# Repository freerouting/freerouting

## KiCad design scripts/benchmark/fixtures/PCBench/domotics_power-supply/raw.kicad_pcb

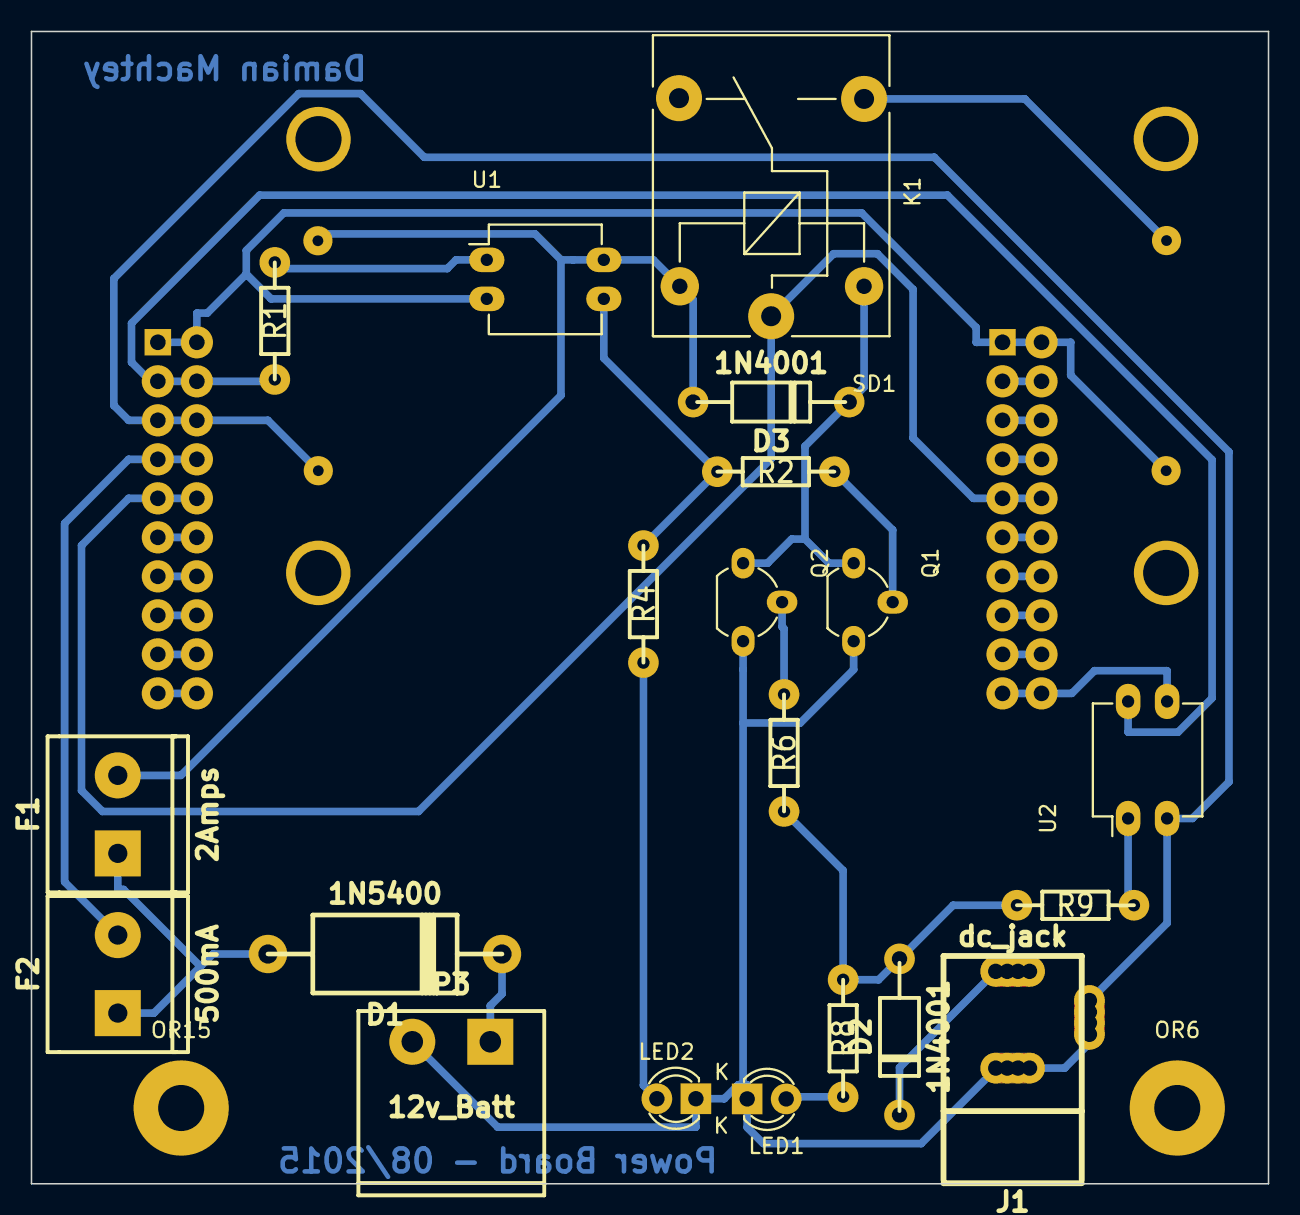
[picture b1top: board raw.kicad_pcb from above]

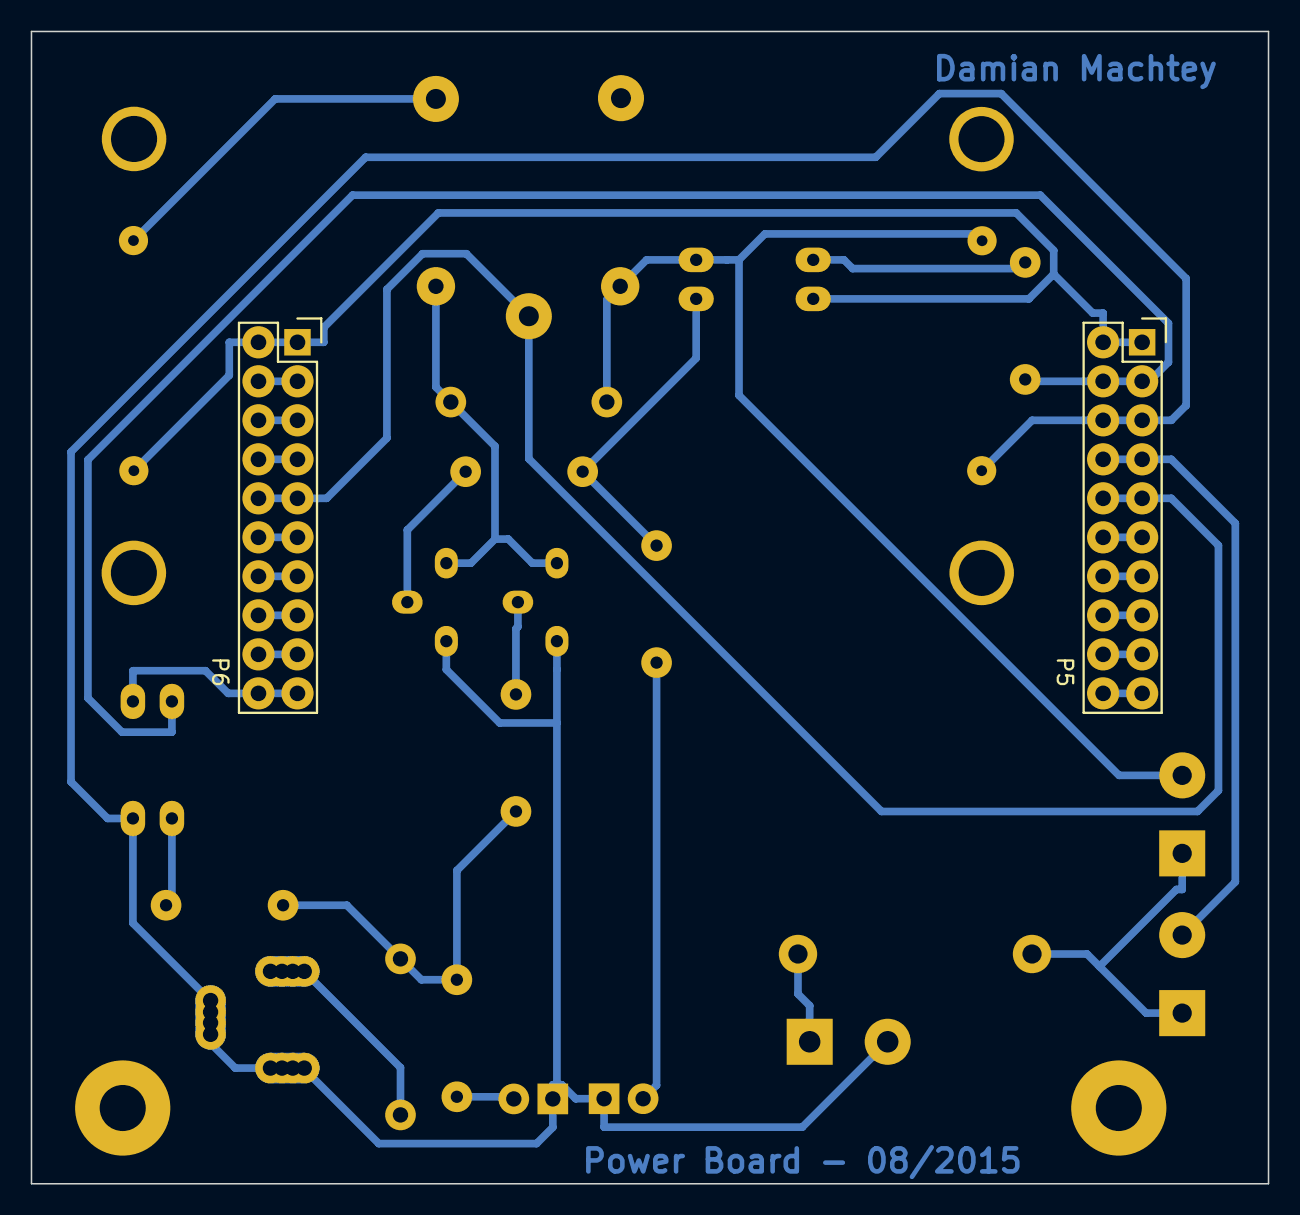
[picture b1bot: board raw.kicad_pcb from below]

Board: 2 copper layers, 80.5 x 75.0 mm, 25 parts (2 on the bottom side), 32 nets.

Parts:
D1: 1N5400; diode_do201
D2, D3: 1N4001; diode_do41
F1: 2Amps; mors_2p
F2: 500mA; mors_2p
J1: dc_jack; dc_socket_rh
K1: 5v Supply; Relay_SANYOU_SRD_Series_Form_C
LED1: Mains; LED-3MM
LED2: BBB; LED-3MM
OR6, OR15: Fix Hole; SolderWirePad_single_2-5mmDrill
P3: 12v_Batt; mstba_2,5%2f2-g-5,08
P5, P6: CONN_02X10; Socket_Strip_Straight_2x10
Q1, Q2: BC547; TO-92_Molded_Wide_Oval
R1: 1K; RC03
R2, R4, R6, R8: 560; RC03
R9: 3k3; RC03
SD1: Step-Down-board; step-down
U1, U2: PC817; DIP-4_W7.62mm_LongPads

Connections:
/12V+: D3.1, F1.2, K1.5, SD1.1, U1.4
/12V+B: F2.2, P5.7, P5.8
/12V+Mains: D2.1, R6.2, R8.2, R9.1
/DC_3.3V: P5.3, P5.4, R1.2, U2.4
/GND: P5.1, P5.2, P6.1, P6.2, SD1.4, U1.2
/GND12V: J1.1, J1.2, LED1.1, LED2.1, P3.2, P5.5, P5.6, Q1.3, Q2.3, SD1.2, U2.2
/GPIO0_7: P6.19, P6.20, U2.3
/VDD_5V: K1.1, P5.9, P5.10, P6.9, P6.10
/VDD_5V-SD: K1.3, SD1.3
unnamed: D1.1, F1.1, F2.1
unnamed: D1.2, P3.1
unnamed: D2.2, J1.3
unnamed: D3.2, K1.2, Q1.1, Q2.1
unnamed: LED1.2, R8.1
unnamed: LED2.2, R4.2
unnamed: P5.11, P5.12
unnamed: P5.13, P5.14
unnamed: P5.15, P5.16
unnamed: P5.17, P5.18
unnamed: P5.19, P5.20
unnamed: P6.3, P6.4
unnamed: P6.5, P6.6
unnamed: P6.7, P6.8
unnamed: P6.11, P6.12
unnamed: P6.13, P6.14
unnamed: P6.15, P6.16
unnamed: P6.17, P6.18
unnamed: Q1.2, R2.2
unnamed: Q2.2, R6.1
unnamed: R1.1, U1.1
unnamed: R2.1, R4.1, U1.3
unnamed: R9.2, U2.1

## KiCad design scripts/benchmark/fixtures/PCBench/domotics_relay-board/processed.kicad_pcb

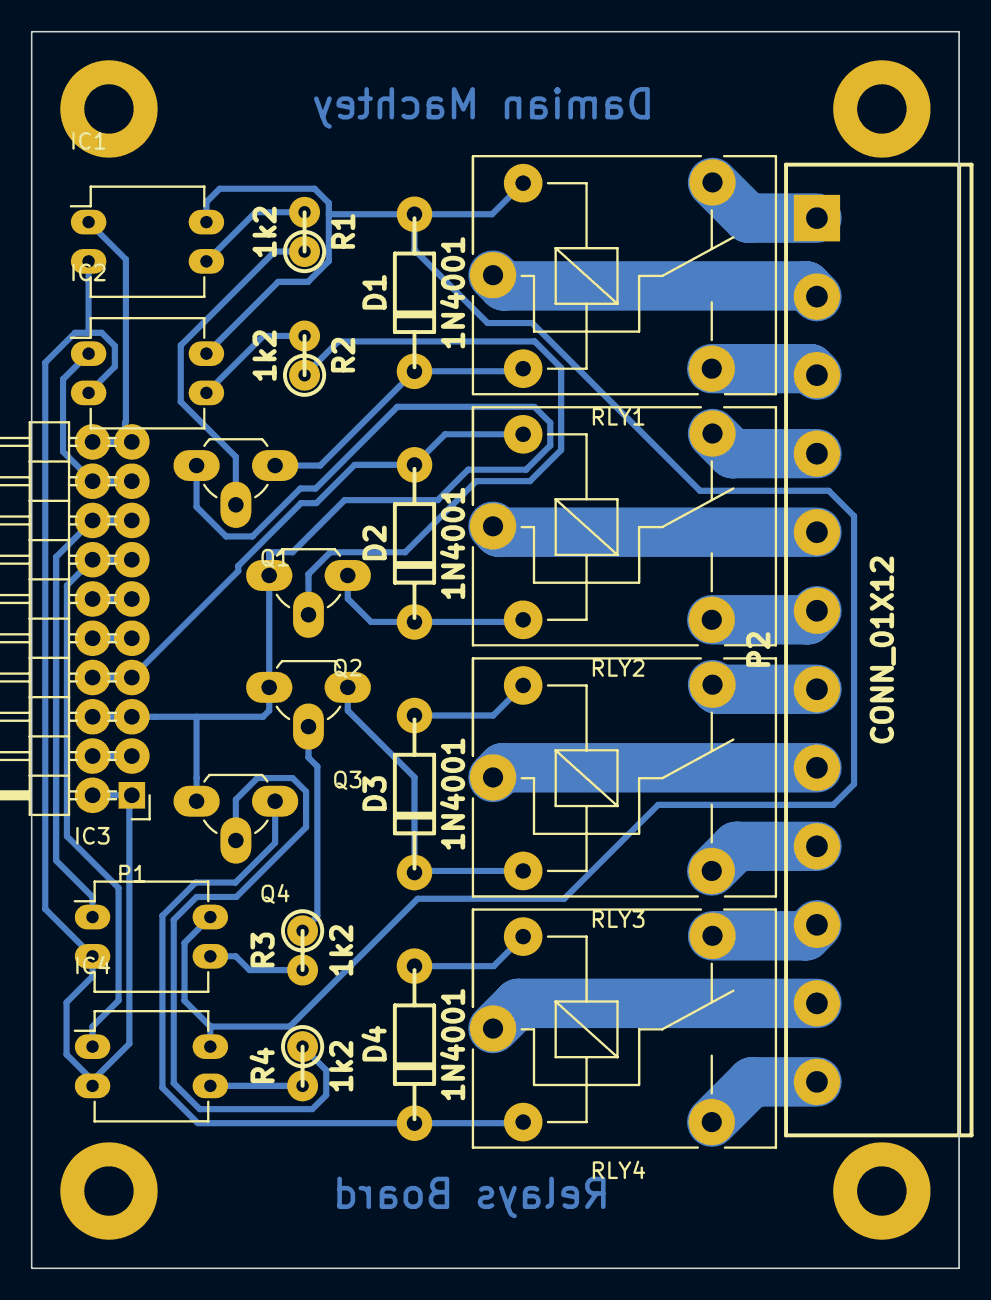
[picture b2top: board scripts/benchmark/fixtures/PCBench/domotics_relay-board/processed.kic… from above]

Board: 2 copper layers, 60.0 x 80.0 mm, 26 parts (0 on the bottom side), 37 nets.

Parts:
D1, D2, D3, D4: 1N4001; diode_do41
IC1, IC2, IC3, IC4: PC817; DIP-4_W7.62mm_LongPads
OR1, OR2, OR3, OR4: SolderWirePad_single_2-5mmDrill
P1: CONN_02X10; Pin_Header_Angled_2x10
P2: CONN_01X12; mstba_2,5%2f12-g-5,08
Q1, Q2, Q3, Q4: BC548; TO-92_Rugged
R1, R2, R3, R4: 1k2; rc05_vert
RLY1, RLY2, RLY3, RLY4: RELAY_HJR-3FF_Z; Relay_SANYOU_SRD_Series_Form_C

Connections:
/3.3V: P1.3, P1.4
/+12VDC: D2.1, P1.7, P1.8, RLY2.5
/GND: IC1.2, IC2.2, IC3.2, IC4.2, P1.1, P1.2
/GND12V: P1.5, P1.6, Q1.3, Q2.3, Q3.3, Q4.3
/in_1: IC1.1, P1.19, P1.20
/in_2: IC2.1, P1.17, P1.18
/in_3: IC3.1, P1.15, P1.16
/in_4: IC4.1, P1.13, P1.14
unnamed: D1.1, IC1.4, IC2.4, IC3.4, IC4.4, RLY1.5
unnamed: D1.2, Q1.1, RLY1.2
unnamed: D2.2, Q2.1, RLY2.2
unnamed: D3.1, RLY3.5
unnamed: D3.2, Q3.1, RLY3.2
unnamed: D4.1, RLY4.5
unnamed: D4.2, Q4.1, RLY4.2
unnamed: IC1.3, R1.2
unnamed: IC2.3, R2.2
unnamed: IC3.3, R3.2
unnamed: IC4.3, R4.2
unnamed: P1.9, P1.10
unnamed: P1.11, P1.12
unnamed: P2.1, RLY1.4
unnamed: P2.2, RLY1.1
unnamed: P2.3, RLY1.3
unnamed: P2.4, RLY2.4
unnamed: P2.5, RLY2.1
unnamed: P2.6, RLY2.3
unnamed: P2.7, RLY3.4
unnamed: P2.8, RLY3.1
unnamed: P2.9, RLY3.3
unnamed: P2.10, RLY4.4
unnamed: P2.11, RLY4.1
unnamed: P2.12, RLY4.3
unnamed: Q1.2, R1.1
unnamed: Q2.2, R2.1
unnamed: Q3.2, R3.1
unnamed: Q4.2, R4.1

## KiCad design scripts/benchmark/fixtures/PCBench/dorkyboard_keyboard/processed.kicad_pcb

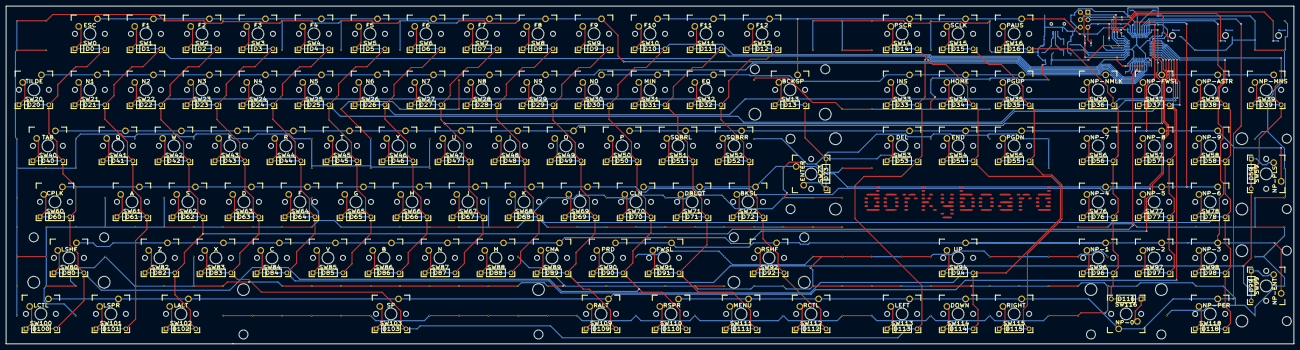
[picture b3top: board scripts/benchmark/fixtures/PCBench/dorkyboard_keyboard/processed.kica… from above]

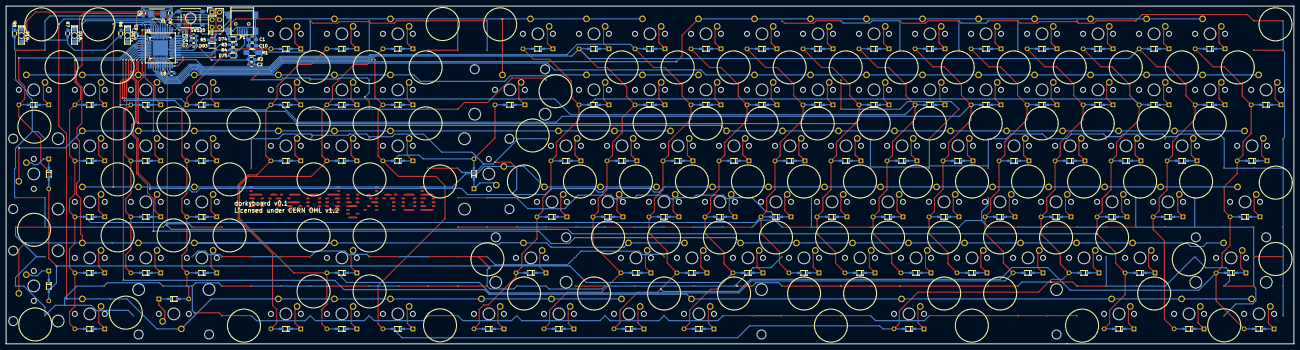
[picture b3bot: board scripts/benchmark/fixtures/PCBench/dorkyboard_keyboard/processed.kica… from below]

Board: 2 copper layers, 436.8 x 114.6 mm, 237 parts (29 on the bottom side), 146 nets.

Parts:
C1, C10: 10uF; C_0805_HandSoldering
C2, C3, C4, C8: 100nF; C_0603_HandSoldering
C5, C6: 22pF; C_0603_HandSoldering
C7, C9: 1uF; C_0603_HandSoldering
D0, D1, D2, D3, D4, D5, D6, D7, D8, D9, D10, D11, D12, D13, D14, D15, D16, D20, D21, D22, D23, D24, D25, D26, D27, D28, D29, D30, D31, D32, D33, D34, D35, D36, D37, D38, D39, D40, D41, D42, D43, D44, D45, D46, D47, D48, D49, D50, D51, D52, D53, D54, D55, D56, D57, D58, D59, D60, D61, D62, D63, D64, D65, D66, D67, D68, D69, D70, D71, D72, D73, D76, D77, D78, D80, D82, D83, D84, D85, D86, D87, D88, D89, D90, D91, D92, D94, D96, D97, D98, D99, D100, D101, D102, D103, D109, D110, D111, D112, D113, D114, D115, D116, D118: D_Small; DIODE_TH-SMT
D17, D18, D19: Led_Small; LED Reverse Mount 3.2x1.6mm Dialight
D74, D75: 6.2V; SOD-323_HandSoldering
D93: 1N4148; SOD-323
P1: USB_MiniB; USB_Mini-B
P2: Do Not Populate; Pin_Header_Straight_2x03
R1: 10R Fusible; R_1206_HandSoldering
R2, R5: 10k; R_0603_HandSoldering
R3, R4: 22R; R_0603_HandSoldering
R6, R7, R8: 604R; R_0603_HandSoldering
SW0: ESC; CHERRY_PCB_100H
SW1: F1; CHERRY_PCB_100H
SW2: F2; CHERRY_PCB_100H
SW3: F3; CHERRY_PCB_100H
SW4: F4; CHERRY_PCB_100H
SW5: F5; CHERRY_PCB_100H
SW6: F6; CHERRY_PCB_100H
SW7: F7; CHERRY_PCB_100H
SW8: F8; CHERRY_PCB_100H
SW9: F9; CHERRY_PCB_100H
SW10: F10; CHERRY_PCB_100H
SW11: F11; CHERRY_PCB_100H
SW12: F12; CHERRY_PCB_100H
SW13: BCKSP; CHERRY_PCB_200H
SW14: PSCR; CHERRY_PCB_100H
SW15: SCLK; CHERRY_PCB_100H
SW16: PAUS; CHERRY_PCB_100H
SW20: TILDE; CHERRY_PCB_100H
SW21: N1; CHERRY_PCB_100H
SW22: N2; CHERRY_PCB_100H
SW23: N3; CHERRY_PCB_100H
SW24: N4; CHERRY_PCB_100H
SW25: N5; CHERRY_PCB_100H
SW26: N6; CHERRY_PCB_100H
SW27: N7; CHERRY_PCB_100H
SW28: N8; CHERRY_PCB_100H
SW29: N9; CHERRY_PCB_100H
SW30: N0; CHERRY_PCB_100H
SW31: MIN; CHERRY_PCB_100H
SW32: EQ; CHERRY_PCB_100H
SW33: INS; CHERRY_PCB_100H
SW34: HOME; CHERRY_PCB_100H
SW35: PGUP; CHERRY_PCB_100H
SW36: NP-NMLK; CHERRY_PCB_100H
SW37: NP-FWSL; CHERRY_PCB_100H
SW38: NP-ASTR; CHERRY_PCB_100H
SW39: NP-MNS; CHERRY_PCB_100H
SW40: TAB; CHERRY_PCB_150H
SW41: Q; CHERRY_PCB_100H
SW42: W; CHERRY_PCB_100H
SW43: E; CHERRY_PCB_100H
SW44: R; CHERRY_PCB_100H
SW45: T; CHERRY_PCB_100H
SW46: Y; CHERRY_PCB_100H
SW47: U; CHERRY_PCB_100H
SW48: I; CHERRY_PCB_100H
SW49: O; CHERRY_PCB_100H
SW50: P; CHERRY_PCB_100H
SW51: SQBRL; CHERRY_PCB_100H
SW52: SQBRR; CHERRY_PCB_100H
SW53: DEL; CHERRY_PCB_100H
SW54: END; CHERRY_PCB_100H
SW55: PGDN; CHERRY_PCB_100H
SW56: NP-7; CHERRY_PCB_100H
SW57: NP-8; CHERRY_PCB_100H
SW58: NP-9; CHERRY_PCB_100H
SW59: NP-PLS; CHERRY_PCB_200V
SW60: CPLK; CHERRY_PCB_175H
SW61: A; CHERRY_PCB_100H
SW62: S; CHERRY_PCB_100H
SW63: D; CHERRY_PCB_100H
SW64: F; CHERRY_PCB_100H
SW65: G; CHERRY_PCB_100H
SW66: H; CHERRY_PCB_100H
SW67: J; CHERRY_PCB_100H
SW68: K; CHERRY_PCB_100H
SW69: L; CHERRY_PCB_100H
SW70: CLN; CHERRY_PCB_100H
SW71: DBLQT; CHERRY_PCB_100H
SW72: BKSL; CHERRY_PCB_100H
SW73: ENTER; CHERRY_PCB_ISOR
SW76: NP-4; CHERRY_PCB_100H
SW77: NP-5; CHERRY_PCB_100H
SW78: NP-6; CHERRY_PCB_100H
SW80: LSHF; CHERRY_PCB_225H
SW82: Z; CHERRY_PCB_100H
SW83: X; CHERRY_PCB_100H
SW84: C; CHERRY_PCB_100H
SW85: V; CHERRY_PCB_100H
SW86: B; CHERRY_PCB_100H
SW87: N; CHERRY_PCB_100H
SW88: M; CHERRY_PCB_100H
SW89: CMA; CHERRY_PCB_100H
SW90: PRD; CHERRY_PCB_100H
SW91: FWSL; CHERRY_PCB_100H
SW92: RSHF; CHERRY_PCB_275H
SW94: UP; CHERRY_PCB_100H
SW96: NP-1; CHERRY_PCB_100H
SW97: NP-2; CHERRY_PCB_100H
SW98: NP-3; CHERRY_PCB_100H
SW99: NP-ENT; CHERRY_PCB_200V
SW100: LCTL; CHERRY_PCB_125H
SW101: LSPR; CHERRY_PCB_125H
SW102: LALT; CHERRY_PCB_125H
SW103: SP; CHERRY_PCB_625H
SW109: RALT; CHERRY_PCB_125H
SW110: RSPR; CHERRY_PCB_125H
SW111: MENU; CHERRY_PCB_125H
SW112: RCTL; CHERRY_PCB_125H
SW113: LEFT; CHERRY_PCB_100H
SW114: DOWN; CHERRY_PCB_100H
SW115: RIGHT; CHERRY_PCB_100H
SW116: NP-0; CHERRY_PCB_200H
SW118: NP-PER; CHERRY_PCB_100H
SW120: SW_P; SW_SPST_PTS645
U1: ATMEGA32U4-M; QFN44-7x7mm-QFP-10x10mm
Y1: 16MHz; Crystal_SMD_5032_2Pads

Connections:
+5V: C9.1, D93.1, P2.2, R5.1, U1.2, U1.14, U1.24, U1.34, U1.44
/matrix/Col0: D0.1, D10.1, D20.1, D30.1, D40.1, D50.1, D60.1, D70.1, D80.1, D90.1, D100.1, D110.1, U1.1
/matrix/Col1: D1.1, D11.1, D21.1, D31.1, D41.1, D51.1, D61.1, D71.1, D91.1, D101.1, D111.1, U1.41
/matrix/Col2: D2.1, D12.1, D22.1, D32.1, D42.1, D52.1, D62.1, D72.1, D82.1, D92.1, D102.1, D112.1, U1.40
/matrix/Col3: D3.1, D13.1, D23.1, D33.1, D43.1, D53.1, D63.1, D73.1, D83.1, D103.1, D113.1, U1.39
/matrix/Col4: D4.1, D14.1, D24.1, D34.1, D44.1, D54.1, D64.1, D84.1, D94.1, D114.1, U1.38
/matrix/Col5: D5.1, D15.1, D25.1, D35.1, D45.1, D55.1, D65.1, D85.1, D115.1, U1.29
/matrix/Col6: D6.1, D16.1, D26.1, D36.1, D46.1, D56.1, D66.1, D76.1, D86.1, D96.1, D116.1, U1.28
/matrix/Col7: D7.1, D27.1, D37.1, D47.1, D57.1, D67.1, D77.1, D87.1, D97.1, U1.27
/matrix/Col8: D8.1, D28.1, D38.1, D48.1, D58.1, D68.1, D78.1, D88.1, D98.1, D118.1, U1.26
/matrix/Col9: D9.1, D29.1, D39.1, D49.1, D59.1, D69.1, D89.1, D99.1, D109.1, U1.25
/matrix/LED0: D17.2, U1.8
/matrix/LED1: D18.2, P2.3, U1.9
/matrix/LED2: D19.2, P2.4, U1.10
/matrix/Row0: SW100.1, SW101.1, SW102.1, SW103.1, SW109.1, U1.30
/matrix/Row1: SW110.1, SW111.1, SW112.1, SW113.1, SW114.1, SW115.1, SW116.1, SW118.1, U1.18
/matrix/Row2: SW80.1, SW82.1, SW83.1, SW84.1, SW85.1, SW86.1, SW87.1, SW88.1, SW89.1, U1.31
/matrix/Row3: SW90.1, SW91.1, SW92.1, SW94.1, SW96.1, SW97.1, SW98.1, SW99.1, U1.19
/matrix/Row4: SW60.1, SW61.1, SW62.1, SW63.1, SW64.1, SW65.1, SW66.1, SW67.1, SW68.1, SW69.1, U1.32
/matrix/Row5: SW70.1, SW71.1, SW72.1, SW73.1, SW76.1, SW77.1, SW78.1, U1.20
/matrix/Row6: SW40.1, SW41.1, SW42.1, SW43.1, SW44.1, SW45.1, SW46.1, SW47.1, SW48.1, SW49.1, U1.33
/matrix/Row7: SW50.1, SW51.1, SW52.1, SW53.1, SW54.1, SW55.1, SW56.1, SW57.1, SW58.1, SW59.1, U1.21
/matrix/Row8: SW20.1, SW21.1, SW22.1, SW23.1, SW24.1, SW25.1, SW26.1, SW27.1, SW28.1, SW29.1, U1.36
/matrix/Row9: SW30.1, SW31.1, SW32.1, SW33.1, SW34.1, SW35.1, SW36.1, SW37.1, SW38.1, SW39.1, U1.22
/matrix/Row10: SW0.1, SW1.1, SW2.1, SW3.1, SW4.1, SW5.1, SW6.1, SW7.1, SW8.1, SW9.1, U1.37
/matrix/Row11: SW10.1, SW11.1, SW12.1, SW13.1, SW14.1, SW15.1, SW16.1, U1.12
/microcontroller/MISO: P2.1, U1.11
/microcontroller/RESET: C3.1, C4.1, D93.2, P2.5, R5.2, SW120.2, U1.13
/microcontroller/VUSB: C2.1, R1.2, R2.1, U1.7
GND: C1.2, C2.2, C3.2, C4.2, C5.2, C6.2, C7.2, C8.2, C9.2, C10.2, D74.2, D75.2, P1.5, P1.6, P2.6, R2.2, R6.2, R7.2, R8.2, SW120.1, U1.5, U1.15, U1.23, U1.35, U1.43, U1.45
unnamed: C1.1, C10.1, P1.1, R1.1
unnamed: C5.1, U1.17, Y1.1
unnamed: C6.1, U1.16, Y1.2
unnamed: C7.1, U1.6
unnamed: C8.1, U1.42
unnamed: D0.2, SW0.2
unnamed: D1.2, SW1.2
unnamed: D2.2, SW2.2
unnamed: D3.2, SW3.2
unnamed: D4.2, SW4.2
unnamed: D5.2, SW5.2
unnamed: D6.2, SW6.2
unnamed: D7.2, SW7.2
unnamed: D8.2, SW8.2
unnamed: D9.2, SW9.2
unnamed: D10.2, SW10.2
unnamed: D11.2, SW11.2
unnamed: D12.2, SW12.2
unnamed: D13.2, SW13.2
unnamed: D14.2, SW14.2
unnamed: D15.2, SW15.2
unnamed: D16.2, SW16.2
unnamed: D17.1, R6.1
unnamed: D18.1, R7.1
unnamed: D19.1, R8.1
unnamed: D20.2, SW20.2
unnamed: D21.2, SW21.2
unnamed: D22.2, SW22.2
unnamed: D23.2, SW23.2
unnamed: D24.2, SW24.2
unnamed: D25.2, SW25.2
unnamed: D26.2, SW26.2
unnamed: D27.2, SW27.2
unnamed: D28.2, SW28.2
unnamed: D29.2, SW29.2
unnamed: D30.2, SW30.2
unnamed: D31.2, SW31.2
unnamed: D32.2, SW32.2
unnamed: D33.2, SW33.2
unnamed: D34.2, SW34.2
unnamed: D35.2, SW35.2
unnamed: D36.2, SW36.2
unnamed: D37.2, SW37.2
unnamed: D38.2, SW38.2
unnamed: D39.2, SW39.2
unnamed: D40.2, SW40.2
unnamed: D41.2, SW41.2
unnamed: D42.2, SW42.2
unnamed: D43.2, SW43.2
unnamed: D44.2, SW44.2
unnamed: D45.2, SW45.2
unnamed: D46.2, SW46.2
unnamed: D47.2, SW47.2
unnamed: D48.2, SW48.2
unnamed: D49.2, SW49.2
unnamed: D50.2, SW50.2
unnamed: D51.2, SW51.2
unnamed: D52.2, SW52.2
unnamed: D53.2, SW53.2
unnamed: D54.2, SW54.2
unnamed: D55.2, SW55.2
unnamed: D56.2, SW56.2
unnamed: D57.2, SW57.2
unnamed: D58.2, SW58.2
unnamed: D59.2, SW59.2
unnamed: D60.2, SW60.2
unnamed: D61.2, SW61.2
unnamed: D62.2, SW62.2
unnamed: D63.2, SW63.2
unnamed: D64.2, SW64.2
unnamed: D65.2, SW65.2
unnamed: D66.2, SW66.2
unnamed: D67.2, SW67.2
unnamed: D68.2, SW68.2
unnamed: D69.2, SW69.2
unnamed: D70.2, SW70.2
unnamed: D71.2, SW71.2
unnamed: D72.2, SW72.2
unnamed: D73.2, SW73.2
unnamed: D74.1, P1.3, R3.1
unnamed: D75.1, P1.2, R4.1
unnamed: D76.2, SW76.2
unnamed: D77.2, SW77.2
unnamed: D78.2, SW78.2
unnamed: D80.2, SW80.2
unnamed: D82.2, SW82.2
unnamed: D83.2, SW83.2
unnamed: D84.2, SW84.2
unnamed: D85.2, SW85.2
unnamed: D86.2, SW86.2
unnamed: D87.2, SW87.2
unnamed: D88.2, SW88.2
unnamed: D89.2, SW89.2
unnamed: D90.2, SW90.2
unnamed: D91.2, SW91.2
unnamed: D92.2, SW92.2
unnamed: D94.2, SW94.2
unnamed: D96.2, SW96.2
unnamed: D97.2, SW97.2
unnamed: D98.2, SW98.2
unnamed: D99.2, SW99.2
unnamed: D100.2, SW100.2
unnamed: D101.2, SW101.2
unnamed: D102.2, SW102.2
unnamed: D103.2, SW103.2
unnamed: D109.2, SW109.2
unnamed: D110.2, SW110.2
unnamed: D111.2, SW111.2
unnamed: D112.2, SW112.2
unnamed: D113.2, SW113.2
unnamed: D114.2, SW114.2
unnamed: D115.2, SW115.2
unnamed: D116.2, SW116.2
unnamed: D118.2, SW118.2
unnamed: R3.2, U1.4
unnamed: R4.2, U1.3

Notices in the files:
scripts/benchmark/fixtures/PCBench/dorkyboard_keyboard/processed.kicad_pcb:
Licensed under CERN OHL v1.2
